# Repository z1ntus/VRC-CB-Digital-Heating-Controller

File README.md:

# VRC-CB Digital Heating Controller

An open-source replacement controller for the **Vaillant VRC-CB** heating controller.

The project replaces the original analogue controller board while retaining the
original plastic controller housing and external wiring. The goal is to provide
a modern, programmable controller without replacing the existing controller
enclosure.

## Main features

* Designed as a replacement PCB for the original VRC-CB controller
* Uses an Arduino Nano ESP32
* Digital control of the original heating-system interface
* Optional room-temperature measurement using an NTC connected to **pins 22 and 23**
* Local temperature/humidity sensing
* Web-based monitoring and control
* Firmware and KiCad hardware design files are provided

## Repository structure

```text
.
├── firmware/                 # Arduino/ESP32 firmware
├── hardware/
│   ├── kicad/                # KiCad schematic and PCB source files
│   ├── gerbers/              # Manufacturing files
│   └── fabrication/          # Drill files, BOM, pick-and-place, etc.
├── docs/                     # Build, installation and technical documentation
├── images/                   # Photos and diagrams
├── LICENSES/                 # License information
├── README.md
└── .gitignore
```

## Hardware

The PCB is intended to fit inside the original VRC-CB plastic housing and to
connect to the existing wiring using the original connector arrangement.

**Important:** Pins 22 and 23 are an optional addition for a room-temperature
NTC. The original controller does not require this connection.

The exact supported NTC type, resistance range and firmware configuration should
be documented in `docs/` before release.

## Software

The firmware is intended for the Arduino Nano ESP32.

## Hardware licence

The KiCad hardware design files are released under:

**CERN Open Hardware Licence Version 2, Strongly Reciprocal
(CERN-OHL-S-2.0)**

See `LICENSES/HARDWARE-LICENSE.md`.

The CERN OHL v2 licence text is maintained by CERN. The definitive licence
text is available from:

https://cern-ohl.web.cern.ch/

## Software license

Software is released under:

**GNU General Public License v3.0 or later (GPL-3.0-or-later)**

See `LICENSES/SOFTWARE-LICENSE.md`.

## Documentation licence

Unless stated otherwise, documentation and original project images are
released under:

**Creative Commons Attribution-ShareAlike 4.0 International
(CC BY-SA 4.0)**

See `LICENSES/DOCUMENTATION-LICENSE.md`.

## Disclaimer

This is an independent hobby/open-hardware project. It is **not affiliated
with, endorsed by, or produced by Vaillant**.

The project is intended for technically competent users who understand the
heating system they are modifying. Working on heating equipment and its
electrical connections can involve serious safety risks.

Do not build or install this controller unless you understand the relevant
electrical, heating-system and local safety requirements. The author provides
the design and software without warranty and accepts no responsibility for
damage, injury or loss resulting from its use.

Before public release, the project documentation should clearly identify the
tested hardware revision, firmware version and supported heating-system
configuration.

## Status

This repository contains a working prototype/controller and is currently being

prepared for its first documented public release.

The hardware and firmware have been tested as a working system. Additional

documentation and manufacturing files will be added incrementally.

The first documented release will include:

* PCB revision
* Firmware version
* Tested Vaillant controller/system configuration
* Arduino Nano ESP32 version
* Sensor configuration
* Known limitations
* Bill of materials
* Build and installation documentation

## Contributions

Issues, suggestions and improvements are welcome. Please open an issue or
pull request on GitHub.

## Parts

A detailed bill of materials will be added to `docs/` or `hardware/` before
the first public release.

Where possible, the exact manufacturer part number should be specified so that
builders can source compatible components independently.

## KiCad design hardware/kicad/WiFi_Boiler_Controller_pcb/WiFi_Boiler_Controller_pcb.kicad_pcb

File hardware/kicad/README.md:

# KiCad source

Place the final KiCad project, schematic and PCB files here.

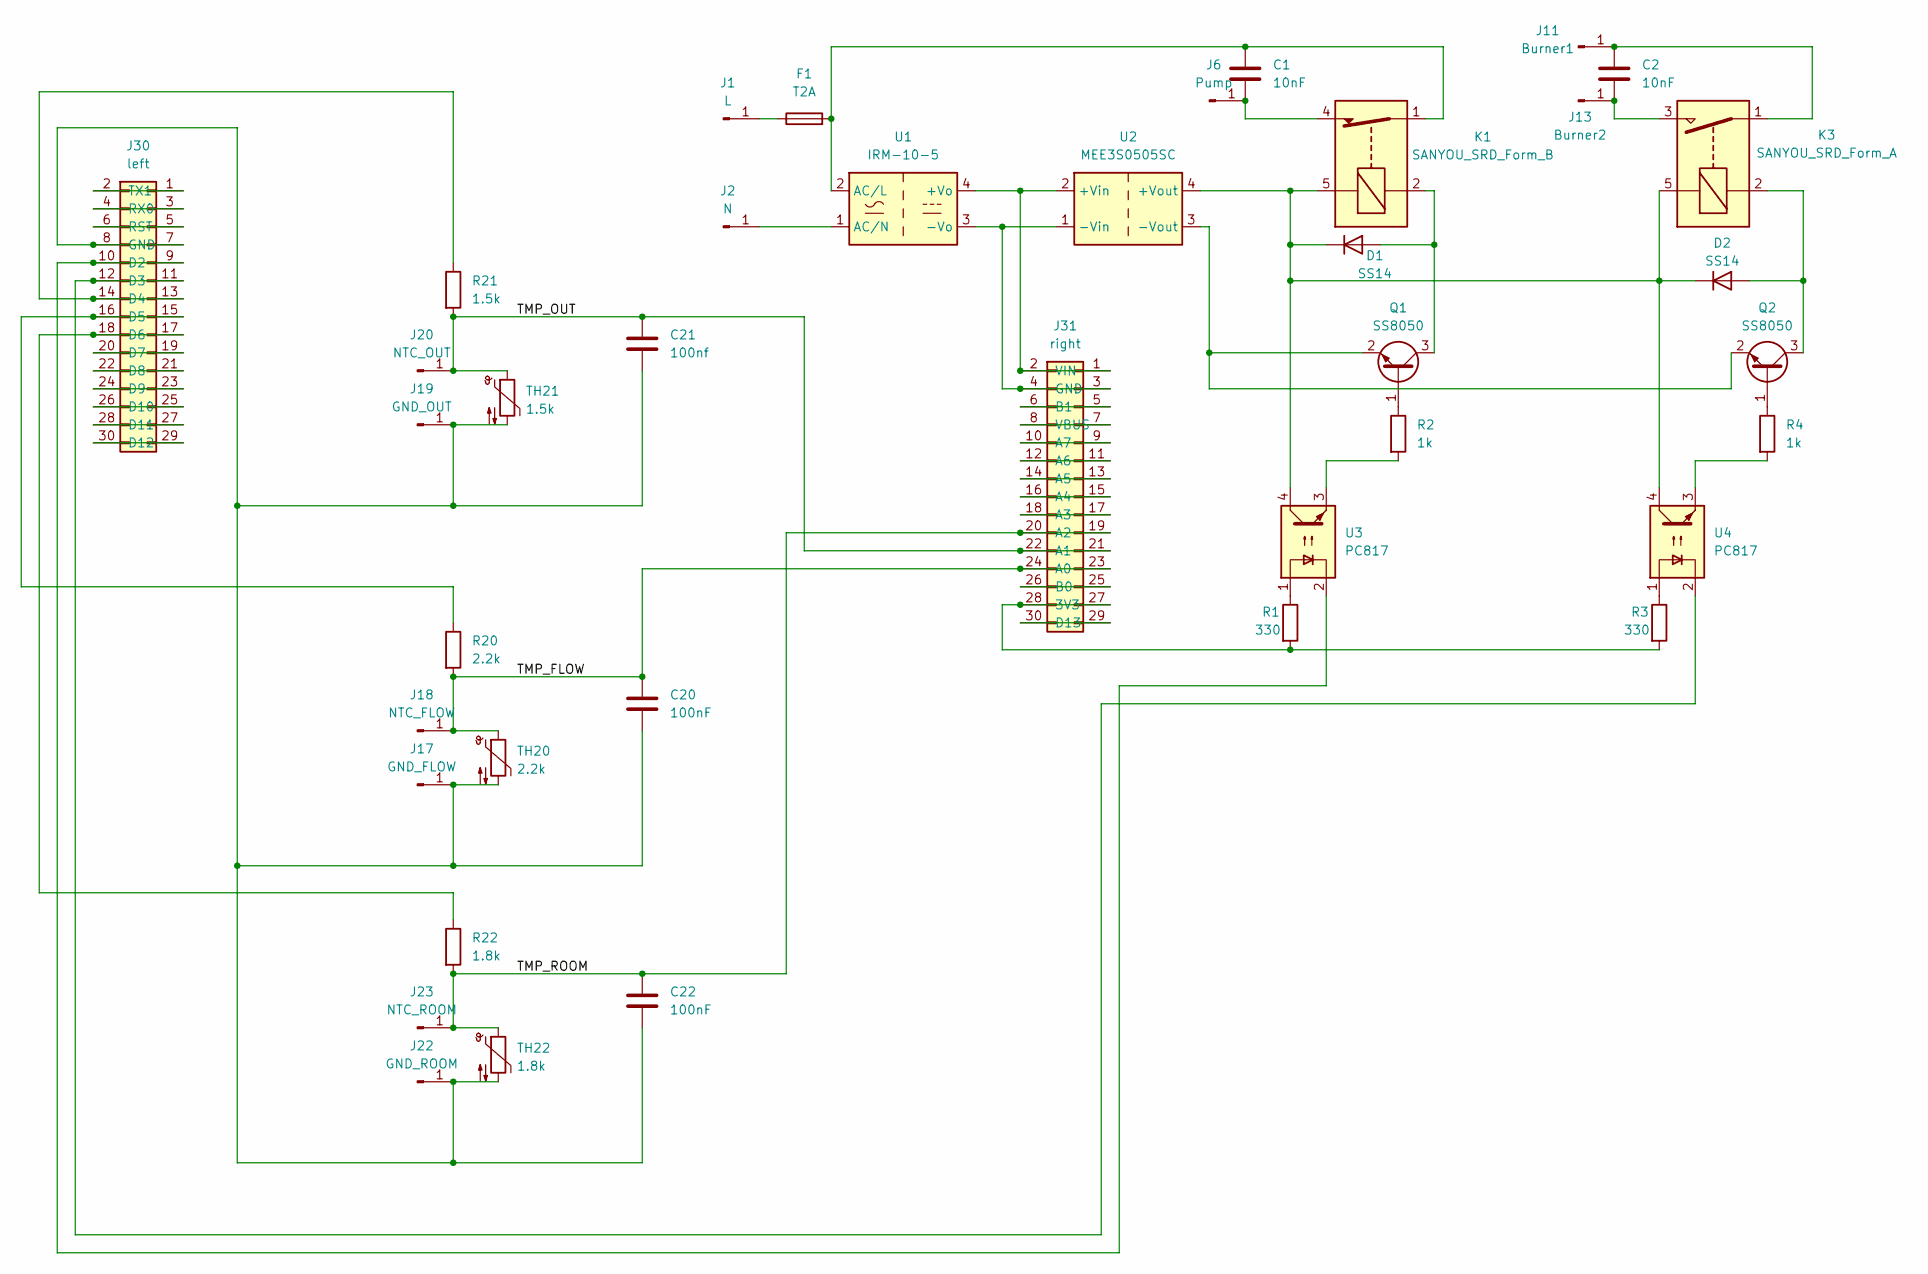
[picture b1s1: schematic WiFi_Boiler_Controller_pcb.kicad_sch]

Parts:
C1, C2: 10nF; C_Rect_L13.0mm_W6.0mm_P10.00mm_FKS3_FKP3_MKS4
C20, C22: 100nF; C_0805_2012Metric
C21: 100nf; C_0805_2012Metric
D1, D2: SS14; D_SOD-123
F1: T2A; Fuseholder_Cylinder-5x20mm_Bulgin_FX0456_Vertical_Closed
J1: L; Faston_Tab_Pad
J2: N; Faston_Tab_Pad
J6: Pump; Faston_Tab_Pad
J11: Burner1; Faston_Tab_Pad
J13: Burner2; Faston_Tab_Pad
J17: GND_FLOW; Faston_Tab_Pad
J18: NTC_FLOW; Faston_Tab_Pad
J19: GND_OUT; Faston_Tab_Pad
J20: NTC_OUT; Faston_Tab_Pad
J22: GND_ROOM; Faston_Tab_Pad
J23: NTC_ROOM; Faston_Tab_Pad
J30: left; PinSocket_2x15_P2.54mm_Vertical
J31: right; PinSocket_2x15_P2.54mm_Vertical
K1: SANYOU_SRD_Form_B; Relay_SPST_SANYOU_SRD_Series_Form_B
K3: SANYOU_SRD_Form_A; Relay_SPST_SANYOU_SRD_Series_Form_A
Q1, Q2: SS8050; SOT-23
R1, R3: 330; R_0805_2012Metric
R2, R4: 1k; R_0805_2012Metric
R20: 2.2k; R_0805_2012Metric
R21: 1.5k; R_0805_2012Metric
R22: 1.8k; R_0805_2012Metric
TH20: 2.2k
TH21: 1.5k
TH22: 1.8k
U1: IRM-10-5; Converter_ACDC_MeanWell_IRM-10-xx_THT
U2: MEE3S0505SC; Converter_DCDC_Murata_MEE3SxxxxSC_THT
U3, U4: PC817; DIP-4_W7.62mm

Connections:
/TMP_FLOW: C20.1, J18.1 (Pin_1_1), J31.23, J31.24 (A0), R20.2, TH20.1
/TMP_OUT: C21.1, J20.1 (Pin_1_1), J31.21, J31.22 (A1), R21.2, TH21.1
/TMP_ROOM: C22.1, J23.1 (Pin_1_1), J31.19, J31.20 (A2), R22.2, TH22.1
unnamed: D1.2 (A), K1.2, Q1.3 (C)
unnamed: D1.1 (K), D2.1 (K), K1.5, K3.5, U2.4 (+Vout), U3.4, U4.4
unnamed: D2.2 (A), K3.2, Q2.3 (C)
unnamed: F1.1, J1.1 (Pin_1_1)
unnamed: J2.1 (Pin_1_1), U1.1 (AC/N)
unnamed: C1.2, J6.1 (Pin_1_1), K1.4
unnamed: C2.1, J11.1 (Pin_1_1), K3.1
unnamed: C2.2, J13.1 (Pin_1_1), K3.3
unnamed: C20.2, C21.2, C22.2, J17.1 (Pin_1_1), J19.1 (Pin_1_1), J22.1 (Pin_1_1), J30.7, J30.8 (GND), TH20.2, TH21.2, TH22.2
unnamed: J30.9, J30.10 (D2), U3.2
unnamed: J30.11, J30.12 (D3), U4.2
unnamed: J30.13, J30.14 (D4), R21.1
unnamed: J30.15, J30.16 (D5), R20.1
unnamed: J30.17, J30.18 (D6), R22.1
unnamed: J30.19, J30.20 (D7)
unnamed: J30.21, J30.22 (D8)
unnamed: J30.23, J30.24 (D9)
unnamed: J30.25, J30.26 (D10)
unnamed: J30.27, J30.28 (D11)
unnamed: J30.29, J30.30 (D12)
unnamed: J30.5, J30.6 (RST)
unnamed: J30.3, J30.4 (RX0)
unnamed: J30.1, J30.2 (TX1)
unnamed: J31.27, J31.28 (3V3), R1.2, R3.2
unnamed: J31.17, J31.18 (A3)
unnamed: J31.15, J31.16 (A4)
unnamed: J31.13, J31.14 (A5)
unnamed: J31.11, J31.12 (A6)
unnamed: J31.9, J31.10 (A7)
unnamed: J31.25, J31.26 (B0)
unnamed: J31.5, J31.6 (B1)
unnamed: J31.29, J31.30 (D13)
unnamed: J31.3, J31.4 (GND), U1.3 (-Vo), U2.1 (-Vin)
unnamed: J31.7, J31.8 (VBUS)
unnamed: J31.1, J31.2 (VIN), U1.4 (+Vo), U2.2 (+Vin)
unnamed: Q1.1 (B), R2.1
unnamed: Q1.2 (E), Q2.2 (E), U2.3 (-Vout)
unnamed: Q2.1 (B), R4.1
unnamed: R1.1, U3.1
unnamed: R2.2, U3.3
unnamed: R3.1, U4.1
unnamed: R4.2, U4.3
unnamed: C1.1, F1.2, K1.1, U1.2 (AC/L)

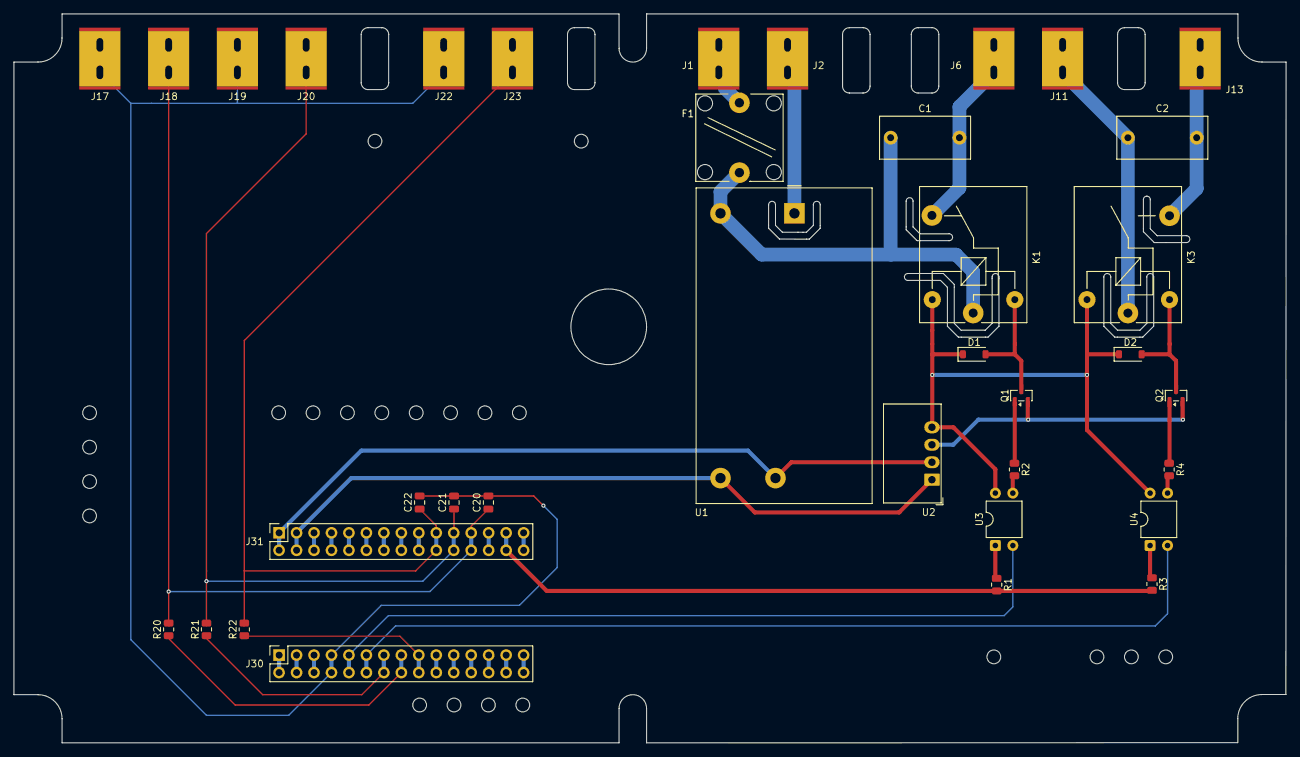
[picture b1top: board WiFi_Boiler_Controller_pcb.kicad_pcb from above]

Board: 2 copper layers, 185.0 x 106.0 mm, 36 parts (0 on the bottom side), 46 nets.
